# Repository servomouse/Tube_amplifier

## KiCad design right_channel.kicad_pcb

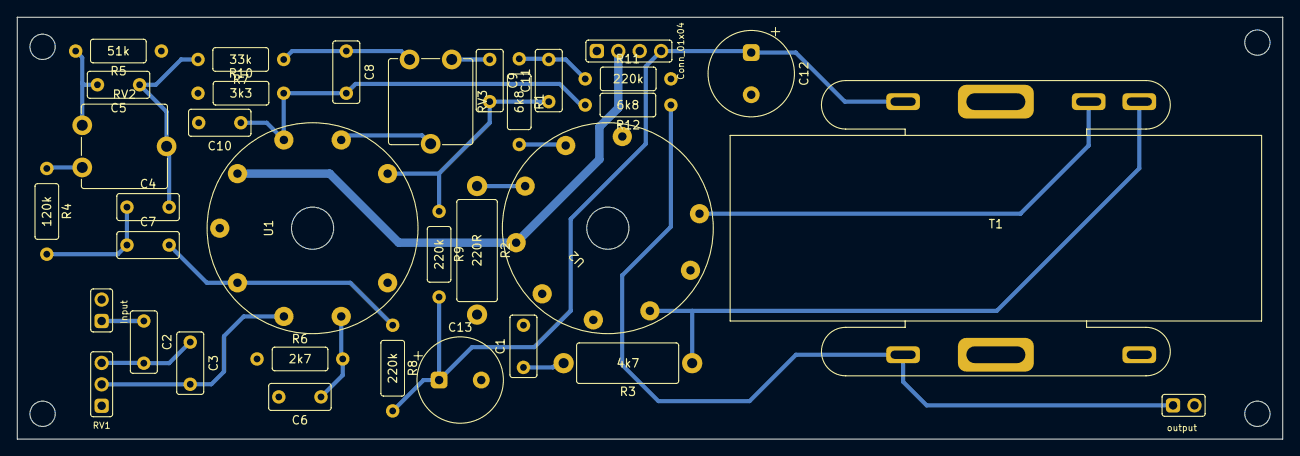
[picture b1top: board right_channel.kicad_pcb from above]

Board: 2 copper layers, 150.0 x 50.0 mm, 34 parts (0 on the bottom side), 24 nets.

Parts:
C1: 1500pF; C_THT_K73-17_P5.00mm
C2: 0,047uF; C_THT_K73-17_P5.00mm
C3: 27pF; C_THT_K73-17_P5.00mm
C4, C8, C10: 2200pF; C_THT_K73-17_P5.00mm
C5: 4700pF; C_THT_K73-17_P5.00mm
C6: 0,01uF; C_THT_K73-17_P5.00mm
C7: 0,033uF; C_THT_K73-17_P5.00mm
C9: 5,6pF; C_THT_K73-17_P5.00mm
C11: 3300pF; C_THT_K73-17_P5.00mm
C12, C13: 10uF; C_THT_D10.0mm_P5.00mm
J2: Input; PinHeader_1x02_P2.54mm
J3: Conn_01x04; PinHeader_1x04_P2.54mm
J4: output; PinHeader_1x02_P2.54mm
R1, R12: 6k8; R_THT_025W
R2: 220R; R_THT_1W
R3: 4k7; R_THT_1W
R4: 120k; R_THT_025W
R5: 51k; R_THT_025W
R6: 2k7; R_THT_025W
R7: 33k; R_THT_025W
R8, R9, R11: 220k; R_THT_025W
R10: 3k3; R_THT_025W
RV1: 470k; PinHeader_1x03_P2.54mm
RV2: 2,2M; Potentiometer_THT_CA9V
RV3: 1M; Potentiometer_THT_CA9V
T1: Transformer_SP_1S; Output_transformer
U1: 6N2P; 9-pin_tube_socket
U2: 6P14P; 9-pin_tube_socket

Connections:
240V: C12.1, C13.1, J3.4, R8.2, R9.2, T1.3 (PR2)
+6V: J3.2, U1.4, U2.4
GND: C1.2, C6.2, C10.2, C12.2, C13.2, J2.2, J3.1, J3.3, J4.2, R2.2, R5.1, R6.1, R10.1, R11.2, RV1.1, T1.5 (S2), U1.5, U1.9, U2.5
Left_output: J4.1, R12.1, T1.4 (S1)
unnamed: C1.1, R3.2
unnamed: C2.1, J2.1
unnamed: C2.2, C3.1, RV1.3
unnamed: C3.2, RV1.2, U1.7
unnamed: C4.1, C7.1, R4.2
unnamed: C4.2, C5.1, R7.2, RV2.2
unnamed: C5.2, R5.2, RV2.3
unnamed: C6.1, R6.2, U1.8
unnamed: C7.2, R8.1, U1.6
unnamed: C8.1, R7.1, RV3.1
unnamed: C9.1, RV3.3
unnamed: C8.2, C10.1, R10.2, R12.2, U1.3
unnamed: C9.2, C11.1, R9.1, U1.1
unnamed: C11.2, R1.1, R11.1
unnamed: R1.2, U2.2
unnamed: R2.1, U2.3
unnamed: R3.1, T1.1 (PR1), U2.7
unnamed: R4.1, RV2.1
unnamed: RV3.2, U1.2
unnamed: T1.2 (PM), U2.9
